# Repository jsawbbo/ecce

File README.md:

# ecce

>    Ecce ex oculis animalis.
    
/ˈek.ke/ Behold! Behold through the eyes of an animal. 

ECCE (Ethological Capture of Creature and Environment) provides the hardware and software infrastructure for animal-borne sensing in freely behaving animals. This repository contains electronic schematics, PCB layouts, CAD designs, embedded firmware, and associated tools for building lightweight, untethered sensor platforms. By capturing environmental and behavioral information from the animal's perspective, ECCE supports neuroethological studies of how sensory input, movement, and neural activity interact to guide natural behavior.

See also: https://github.com/bbo-lab/vidre

**Status**: Planning stage...

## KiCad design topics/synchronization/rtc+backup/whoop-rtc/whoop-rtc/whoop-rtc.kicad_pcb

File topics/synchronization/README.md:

# Synchronization

Circuits, firmware, code and notes with regard to sensor and signal synchronization.

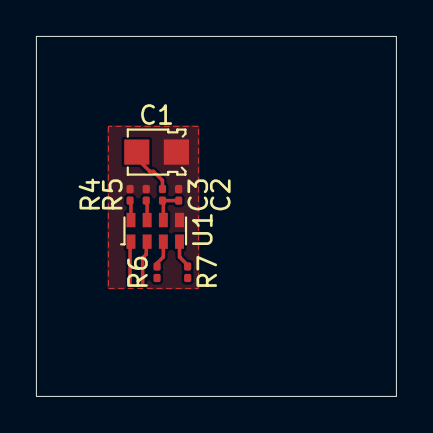
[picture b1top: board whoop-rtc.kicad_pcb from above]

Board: 2 copper layers, 20.0 x 20.0 mm, 8 parts (0 on the bottom side), 8 nets.

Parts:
C1: 11m; CPH3225A
C2, C3: 100n; C_0201_0603Metric
R4: 10k; R_0201_0603Metric
R5: 100; R_0201_0603Metric
R6, R7: 2k2; R_0201_0603Metric
U1: RV-4162-C7-TA-QC-020; RV-3028-C7

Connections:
/EVI: R4.1, U1.8 (EVI)
/SCL: R6.2, U1.3 (SCL)
/SDA: R7.2, U1.4 (SDA)
/V_{IO}: R6.1, R7.1
/V_{SUP}: C3.2, U1.7 (VDD)
/V_{backup}: C2.1, R5.1, U1.6 (Vbackup)
GND: C1.2, C2.2, C3.1, R4.2, U1.5 (VSS)
unnamed: C1.1, R5.2

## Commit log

2026-06-06 readme
2026-06-06 Update README with improved phrasing
2026-06-06 added RTC clock from whoop project
2026-06-06 text
2026-06-07 Update README.md for clarity and formatting
